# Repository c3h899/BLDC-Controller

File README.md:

# Introduction
A basic implementation of a half-bridge driver for hobbyest DC motors.

## Features of Interest
* Isolated, Schmitt Trigger, Digital Input
* Designed for 3-phase operation of upto 2 HP
* Nominally, functional upto a few 100 kHz* 
* Mild protection from cross-conduction

## Summary of Critical Parts
* Isolated ADUM7234 Gate Driver
* 74HC7002 Schmitt-Trigger Input Stage
* BUK9T14-80E N-Channel MOSFET(s)
* NO Back-EMF Sensing

## Nominal Operation
* (12 to 30) V Drive input
* Several Amps (Heatsinking Required)
* **Expectes** Proper cross-conduction prevention measures in software

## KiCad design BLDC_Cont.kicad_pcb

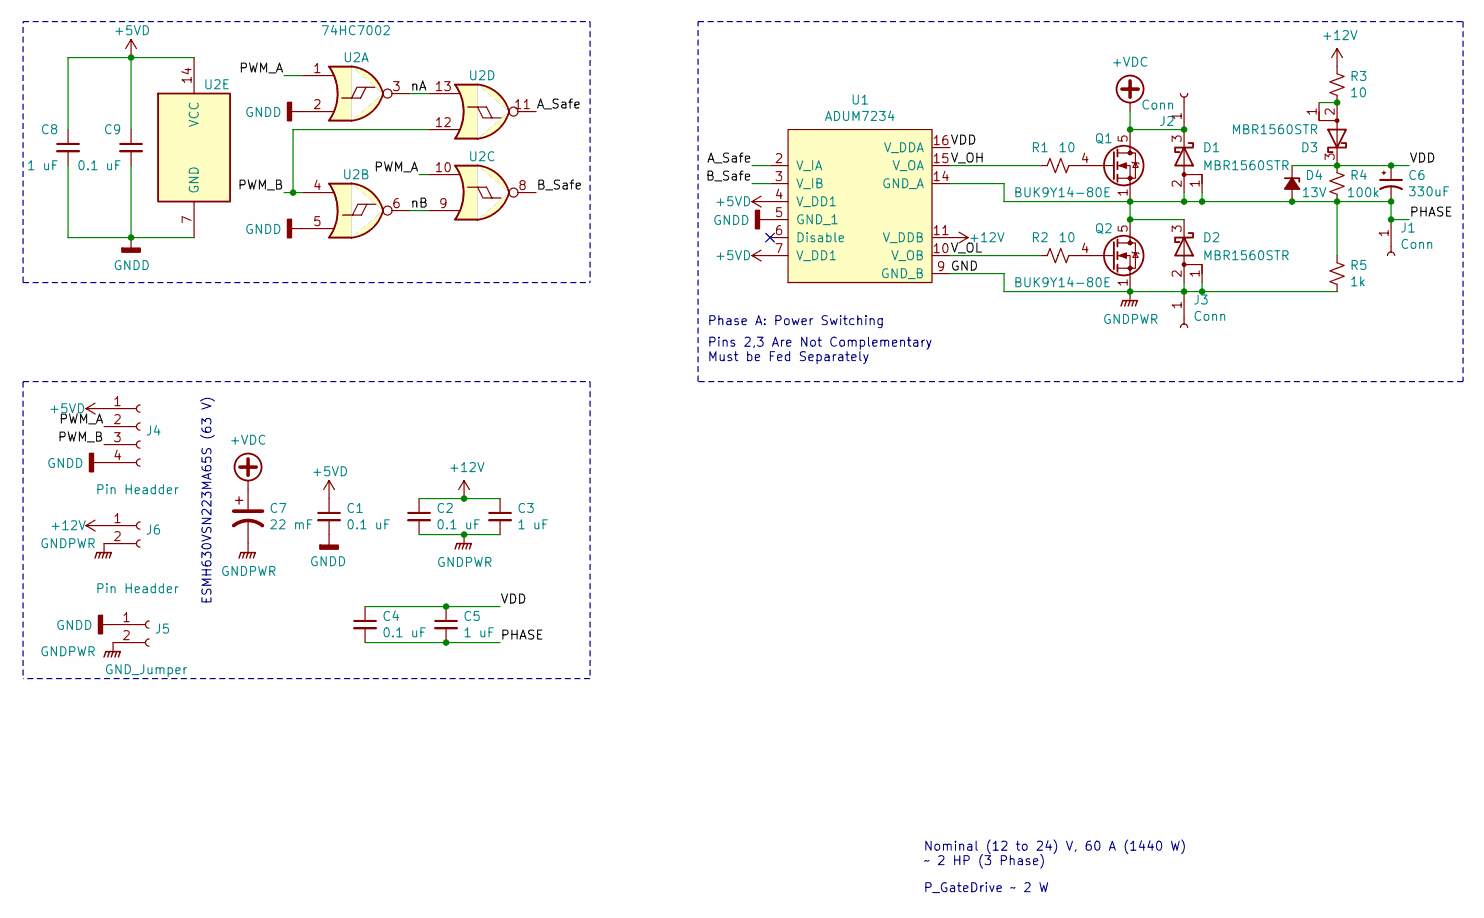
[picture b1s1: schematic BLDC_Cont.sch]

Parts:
C1, C2, C4, C9: 0.1 uF; C_1206_3216Metric_Pad1.33x1.80mm_HandSolder
C3, C5, C8: 1 uF; C_1206_3216Metric_Pad1.33x1.80mm_HandSolder
C6: 330uF; CP_Radial_D6.3mm_P2.50mm
C7: 22 mF; CP_Radial_D35.0mm_P10.00mm_SnapIn
D1, D2, D3: MBR1560STR; TO-277B
D4: 13V; D_SOD-123
J1, J2, J3: Conn; TestPoint_Pad_4.0x4.0mm
J4: Pin Headder; PinHeader_1x04_P2.54mm_Vertical
J5: GND_Jumper; SolderJumper-2_P1.3mm_Open_Pad1.0x1.5mm
J6: Pin Headder; PinHeader_1x02_P2.54mm_Vertical
Q1, Q2: BUK9Y14-80E; LFPAK56
R1, R2, R3: 10; R_1206_3216Metric_Pad1.30x1.75mm_HandSolder
R4: 100k; R_1206_3216Metric_Pad1.30x1.75mm_HandSolder
R5: 1k; R_1206_3216Metric_Pad1.30x1.75mm_HandSolder
U1: ADUM7234; SOIC-16_3.9x9.9mm_P1.27mm
U2: 74HC7002; SOIC-14_3.9x8.7mm_P1.27mm

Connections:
+5VD: C1.1, C8.1, C9.1, J4.1, U1.4 (V_DD1), U1.7 (V_DD1), U2.14 (VCC)
+12V: C2.1, C3.1, J6.1, R3.2, U1.11 (V_DDB)
+VDC: C7.1, D1.3 (K), J2.1, Q1.5 (D)
/A_Safe: U1.2 (V_IA), U2.11
/B_Safe: U1.3 (V_IB), U2.8
/PHASE: C4.2, C5.2, C6.2, D1.1 (A), D1.2 (A), D2.3 (K), D4.2 (A), J1.1, Q1.1 (S), Q1.2 (S), Q1.3 (S), Q2.5 (D), R4.2, R5.1, U1.14 (GND_A)
/PWM_A: J4.2, U2.1, U2.10
/PWM_B: J4.3, U2.4, U2.12
/VDD: C4.1, C5.1, C6.1, D3.3 (K), D4.1 (K), R4.1, U1.16 (V_DDA)
/V_OH: R1.2, U1.15 (V_OA)
/V_OL: R2.2, U1.10 (V_OB)
/nA: U2.3, U2.13
/nB: U2.6, U2.9
GNDD: C1.2, C8.2, C9.2, J4.4, J5.1, U1.5 (GND_1), U2.2, U2.5, U2.7 (GND)
GNDPWR: C2.2, C3.2, C7.2, D2.1 (A), D2.2 (A), J3.1, J5.2, J6.2, Q2.1 (S), Q2.2 (S), Q2.3 (S), R5.2, U1.9 (GND_B)
unnamed: D3.1 (A), D3.2 (A), R3.1
unnamed: Q1.4 (G), R1.1
unnamed: Q2.4 (G), R2.1

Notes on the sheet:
Nominal (12 to 24) V, 60 A (1440 W) ~~ 2 HP (3 Phase)
P_GateDrive ~~ 2 W
Phase A: Power Switching
ESMH630VSN223MA65S (63 V)
Pins 2,3 Are Not Complementary Must be Fed Separately

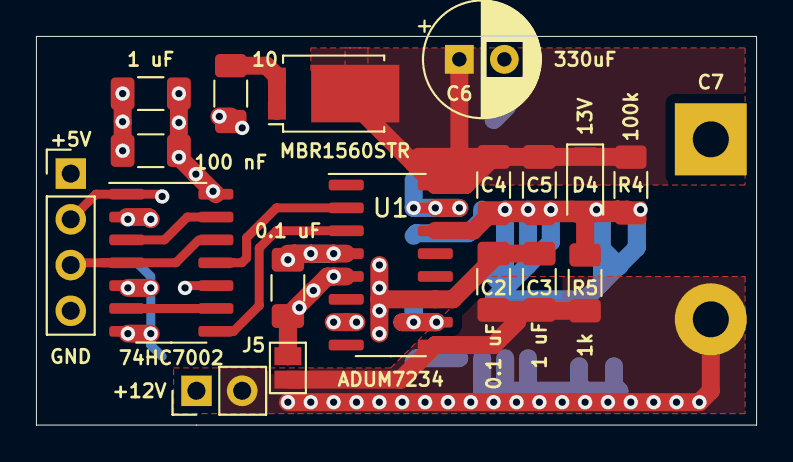
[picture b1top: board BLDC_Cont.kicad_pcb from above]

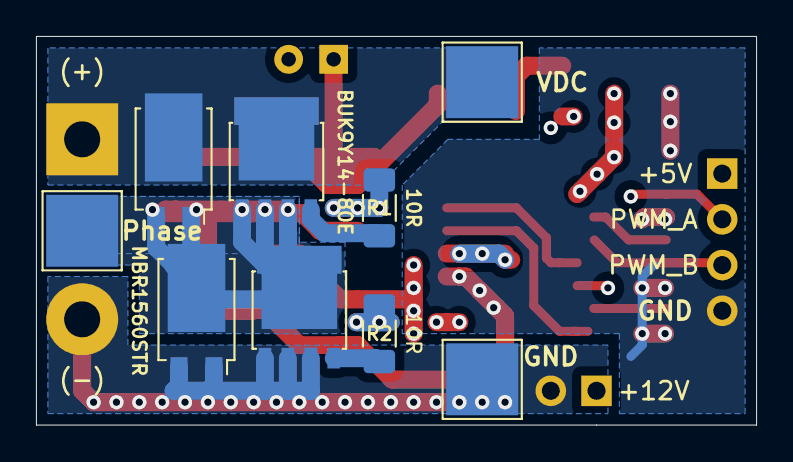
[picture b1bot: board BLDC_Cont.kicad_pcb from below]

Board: 4 copper layers, 40.0 x 21.6 mm, 28 parts (9 on the bottom side), 18 nets.

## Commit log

2021-11-07 Initial Upload
    Initial Upload of Project Initially Investigated in October
    Still in prototype construction & verification phase.
2021-11-15 Rev. 3
    Updated Revision (3)
    -Organized files
    -Removed legacy documentation
    -Found cross-conduction protection of ADuM7234 was **NOT** satisfactory.
    +Added NOR gate based mutual exclusion circuit.
2021-11-15 Update README.md
    Spelling
